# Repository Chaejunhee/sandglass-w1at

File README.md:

# sandglass-w1at
mechanical keyboard inspired by sandglass and w1at

https://youtu.be/1iDzc6l8_Gc?si=unHlyYpFCyEGt74x

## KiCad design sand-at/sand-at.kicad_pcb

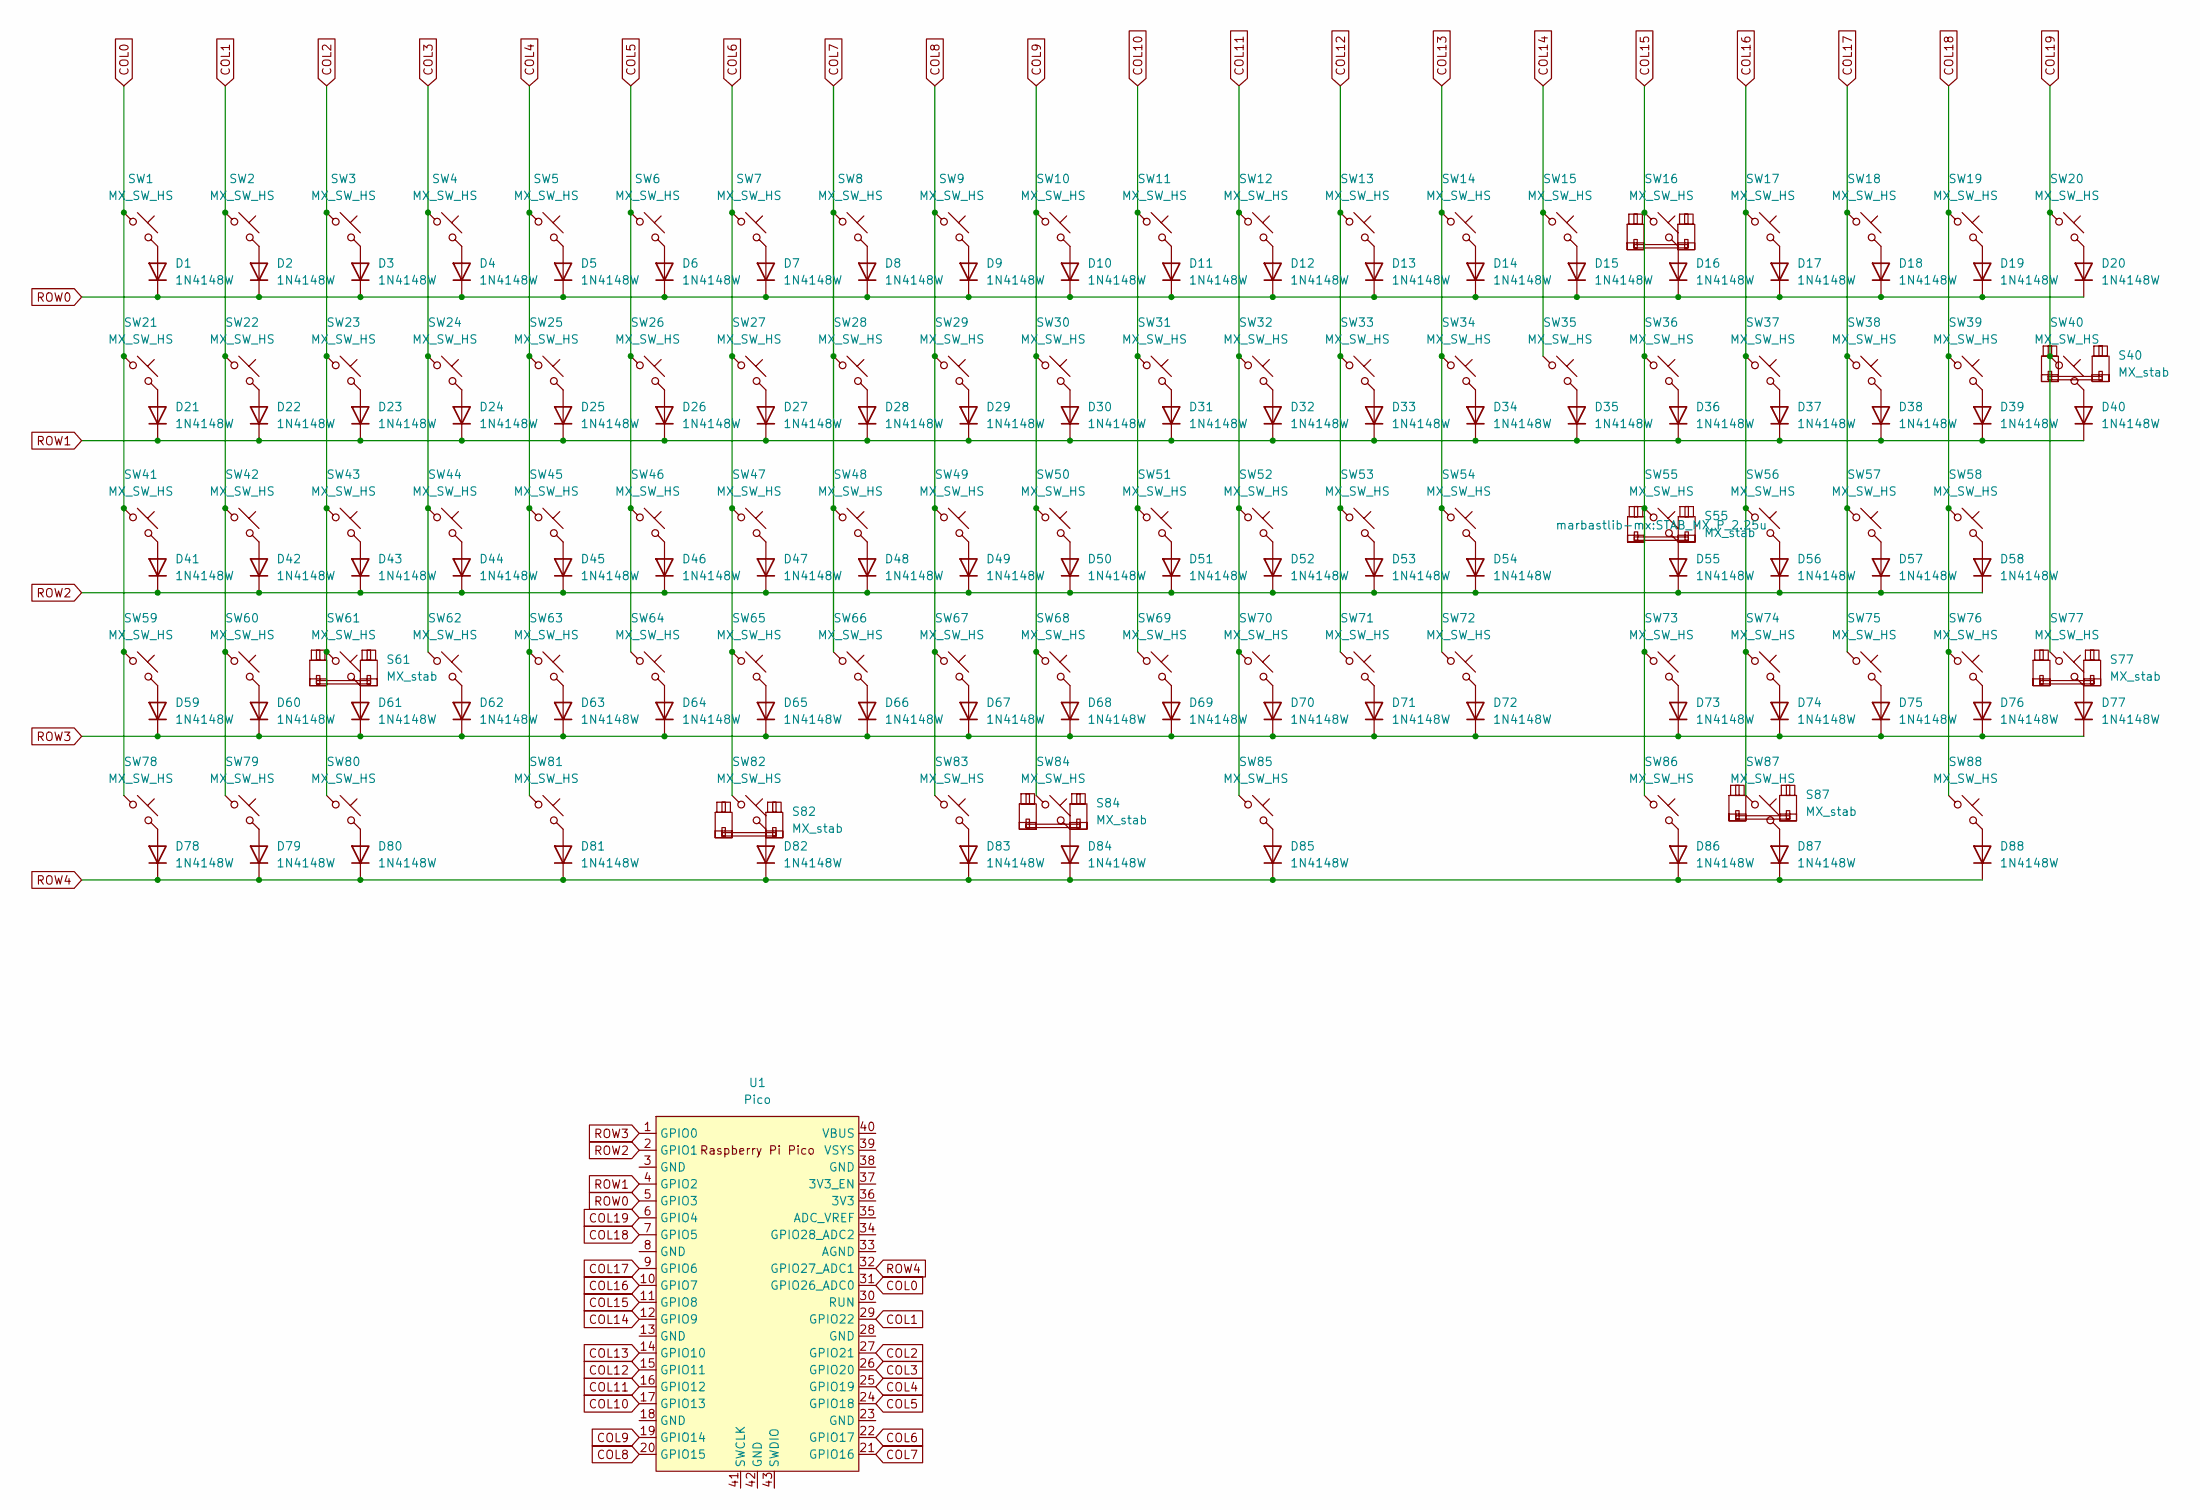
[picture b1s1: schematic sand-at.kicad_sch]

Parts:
D1, D2, D3, D4, D5, D6, D7, D8, D9, D10, D11, D12, D13, D14, D15, D16, D17, D18, D19, D20, D21, D22, D23, D24, D25, D26, D27, D28, D29, D30, D31, D32, D33, D34, D35, D36, D37, D38, D39, D40, D41, D42, D43, D44, D45, D46, D47, D48, D49, D50, D51, D52, D53, D54, D55, D56, D57, D58, D59, D60, D61, D62, D63, D64, D65, D66, D67, D68, D69, D70, D71, D72, D73, D74, D75, D76, D77, D78, D79, D80, D81, D82, D83, D84, D85, D86, D87, D88: 1N4148W; D_SOD-123
S16, S40, S77, S87: MX_stab; STAB_MX_P_2u
S55, S61, S84: MX_stab; STAB_MX_P_2.25u
S82: MX_stab; STAB_MX_P_2.75u
SW1, SW2, SW3, SW4, SW5, SW6, SW7, SW8, SW9, SW10, SW11, SW12, SW13, SW14, SW15, SW16, SW17, SW18, SW19, SW20, SW21, SW22, SW23, SW24, SW25, SW26, SW27, SW28, SW29, SW30, SW31, SW32, SW33, SW34, SW35, SW36, SW37, SW38, SW39, SW40, SW41, SW42, SW43, SW44, SW45, SW46, SW47, SW48, SW49, SW50, SW51, SW52, SW53, SW54, SW55, SW56, SW57, SW58, SW59, SW60, SW61, SW62, SW63, SW64, SW65, SW66, SW67, SW68, SW69, SW70, SW71, SW72, SW73, SW74, SW75, SW76, SW77, SW78, SW79, SW80, SW81, SW82, SW83, SW84, SW85, SW86, SW87, SW88: MX_SW_HS; mxswitch_1u_hotswap
U1: Pico; RPi_Pico_SMD_TH

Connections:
COL0: SW1.1, SW21.1, SW41.1, SW59.1, SW78.1, U1.31 (GPIO26_ADC0)
COL1: SW2.1, SW22.1, SW42.1, SW60.1, SW79.1, U1.29 (GPIO22)
COL2: SW3.1, SW23.1, SW43.1, SW61.1, SW80.1, U1.27 (GPIO21)
COL3: SW4.1, SW24.1, SW44.1, SW62.1, U1.26 (GPIO20)
COL4: SW5.1, SW25.1, SW45.1, SW63.1, SW81.1, U1.25 (GPIO19)
COL5: SW6.1, SW26.1, SW46.1, SW64.1, U1.24 (GPIO18)
COL6: SW7.1, SW27.1, SW47.1, SW65.1, SW82.1, U1.22 (GPIO17)
COL7: SW8.1, SW28.1, SW48.1, SW66.1, U1.21 (GPIO16)
COL8: SW9.1, SW29.1, SW49.1, SW67.1, SW83.1, U1.20 (GPIO15)
COL9: SW10.1, SW30.1, SW50.1, SW68.1, SW84.1, U1.19 (GPIO14)
COL10: SW11.1, SW31.1, SW51.1, SW69.1, U1.17 (GPIO13)
COL11: SW12.1, SW32.1, SW52.1, SW70.1, SW85.1, U1.16 (GPIO12)
COL12: SW13.1, SW33.1, SW53.1, SW71.1, U1.15 (GPIO11)
COL13: SW14.1, SW34.1, SW54.1, SW72.1, U1.14 (GPIO10)
COL14: SW15.1, SW35.1, U1.12 (GPIO9)
COL15: SW16.1, SW36.1, SW55.1, SW73.1, SW86.1, U1.11 (GPIO8)
COL16: SW17.1, SW37.1, SW56.1, SW74.1, SW87.1, U1.10 (GPIO7)
COL17: SW18.1, SW38.1, SW57.1, SW75.1, U1.9 (GPIO6)
COL18: SW19.1, SW39.1, SW58.1, SW76.1, SW88.1, U1.7 (GPIO5)
COL19: SW20.1, SW40.1, SW77.1, U1.6 (GPIO4)
unnamed: D1.2 (A), SW1.2
unnamed: D2.2 (A), SW2.2
unnamed: D3.2 (A), SW3.2
unnamed: D4.2 (A), SW4.2
unnamed: D5.2 (A), SW5.2
unnamed: D6.2 (A), SW6.2
unnamed: D7.2 (A), SW7.2
unnamed: D8.2 (A), SW8.2
unnamed: D9.2 (A), SW9.2
unnamed: D10.2 (A), SW10.2
unnamed: D11.2 (A), SW11.2
unnamed: D12.2 (A), SW12.2
unnamed: D13.2 (A), SW13.2
unnamed: D14.2 (A), SW14.2
unnamed: D15.2 (A), SW15.2
unnamed: D16.2 (A), SW16.2
unnamed: D17.2 (A), SW17.2
unnamed: D18.2 (A), SW18.2
unnamed: D19.2 (A), SW19.2
unnamed: D20.2 (A), SW20.2
unnamed: D21.2 (A), SW21.2
unnamed: D22.2 (A), SW22.2
unnamed: D23.2 (A), SW23.2
unnamed: D24.2 (A), SW24.2
unnamed: D25.2 (A), SW25.2
unnamed: D26.2 (A), SW26.2
unnamed: D27.2 (A), SW27.2
unnamed: D28.2 (A), SW28.2
unnamed: D29.2 (A), SW29.2
unnamed: D30.2 (A), SW30.2
unnamed: D31.2 (A), SW31.2
unnamed: D32.2 (A), SW32.2
unnamed: D33.2 (A), SW33.2
unnamed: D34.2 (A), SW34.2
unnamed: D35.2 (A), SW35.2
unnamed: D36.2 (A), SW36.2
unnamed: D37.2 (A), SW37.2
unnamed: D38.2 (A), SW38.2
unnamed: D39.2 (A), SW39.2
unnamed: D40.2 (A), SW40.2
unnamed: D41.2 (A), SW41.2
unnamed: D42.2 (A), SW42.2
unnamed: D43.2 (A), SW43.2
unnamed: D44.2 (A), SW44.2
unnamed: D45.2 (A), SW45.2
unnamed: D46.2 (A), SW46.2
unnamed: D47.2 (A), SW47.2
unnamed: D48.2 (A), SW48.2
unnamed: D49.2 (A), SW49.2
unnamed: D50.2 (A), SW50.2
unnamed: D51.2 (A), SW51.2
unnamed: D52.2 (A), SW52.2
unnamed: D53.2 (A), SW53.2
unnamed: D54.2 (A), SW54.2
unnamed: D55.2 (A), SW55.2
unnamed: D56.2 (A), SW56.2
unnamed: D57.2 (A), SW57.2
unnamed: D58.2 (A), SW58.2
unnamed: D59.2 (A), SW59.2
unnamed: D60.2 (A), SW60.2
unnamed: D61.2 (A), SW61.2
unnamed: D62.2 (A), SW62.2
unnamed: D63.2 (A), SW63.2
unnamed: D64.2 (A), SW64.2
unnamed: D65.2 (A), SW65.2
unnamed: D66.2 (A), SW66.2
unnamed: D67.2 (A), SW67.2
unnamed: D68.2 (A), SW68.2
unnamed: D69.2 (A), SW69.2
unnamed: D70.2 (A), SW70.2
unnamed: D71.2 (A), SW71.2
unnamed: D72.2 (A), SW72.2
unnamed: D73.2 (A), SW73.2
unnamed: D74.2 (A), SW74.2
unnamed: D75.2 (A), SW75.2
unnamed: D76.2 (A), SW76.2
unnamed: D77.2 (A), SW77.2
unnamed: D78.2 (A), SW78.2
unnamed: D79.2 (A), SW79.2
unnamed: D80.2 (A), SW80.2
unnamed: D81.2 (A), SW81.2
unnamed: D82.2 (A), SW82.2
unnamed: D83.2 (A), SW83.2
unnamed: D84.2 (A), SW84.2
unnamed: D85.2 (A), SW85.2
unnamed: D86.2 (A), SW86.2
unnamed: D87.2 (A), SW87.2
unnamed: D88.2 (A), SW88.2
ROW0: D1.1 (K), D2.1 (K), D3.1 (K), D4.1 (K), D5.1 (K), D6.1 (K), D7.1 (K), D8.1 (K), D9.1 (K), D10.1 (K), D11.1 (K), D12.1 (K), D13.1 (K), D14.1 (K), D15.1 (K), D16.1 (K), D17.1 (K), D18.1 (K), D19.1 (K), D20.1 (K), U1.5 (GPIO3)
ROW1: D21.1 (K), D22.1 (K), D23.1 (K), D24.1 (K), D25.1 (K), D26.1 (K), D27.1 (K), D28.1 (K), D29.1 (K), D30.1 (K), D31.1 (K), D32.1 (K), D33.1 (K), D34.1 (K), D35.1 (K), D36.1 (K), D37.1 (K), D38.1 (K), D39.1 (K), D40.1 (K), U1.4 (GPIO2)
ROW2: D41.1 (K), D42.1 (K), D43.1 (K), D44.1 (K), D45.1 (K), D46.1 (K), D47.1 (K), D48.1 (K), D49.1 (K), D50.1 (K), D51.1 (K), D52.1 (K), D53.1 (K), D54.1 (K), D55.1 (K), D56.1 (K), D57.1 (K), D58.1 (K), U1.2 (GPIO1)
ROW3: D59.1 (K), D60.1 (K), D61.1 (K), D62.1 (K), D63.1 (K), D64.1 (K), D65.1 (K), D66.1 (K), D67.1 (K), D68.1 (K), D69.1 (K), D70.1 (K), D71.1 (K), D72.1 (K), D73.1 (K), D74.1 (K), D75.1 (K), D76.1 (K), D77.1 (K), U1.1 (GPIO0)
ROW4: D78.1 (K), D79.1 (K), D80.1 (K), D81.1 (K), D82.1 (K), D83.1 (K), D84.1 (K), D85.1 (K), D86.1 (K), D87.1 (K), D88.1 (K), U1.32 (GPIO27_ADC1)

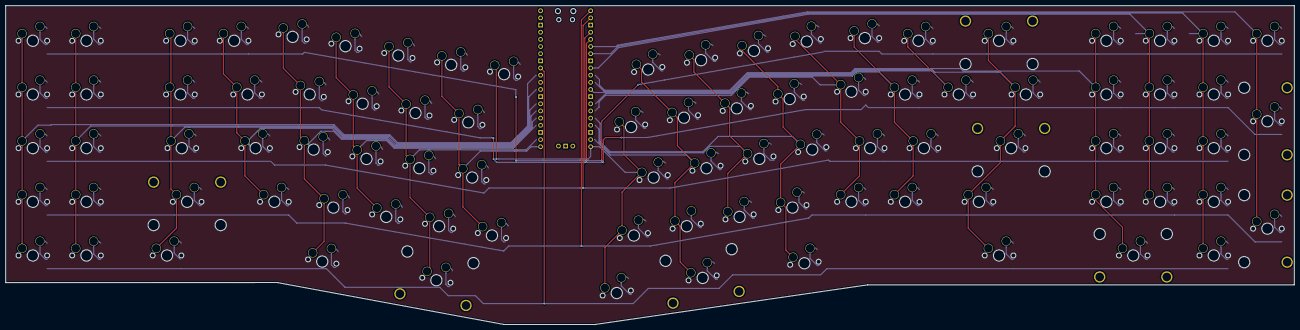
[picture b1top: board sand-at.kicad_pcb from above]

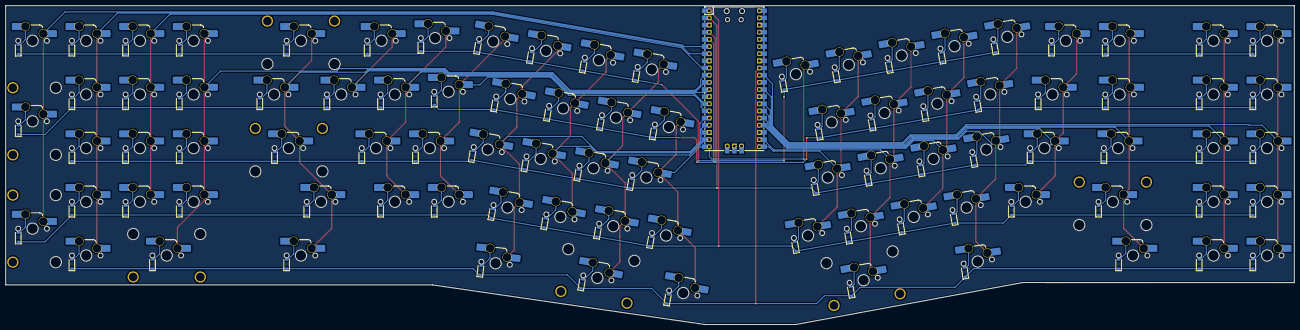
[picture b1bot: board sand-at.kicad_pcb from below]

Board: 2 copper layers, 457.3 x 113.1 mm, 185 parts (89 on the bottom side), 113 nets.
